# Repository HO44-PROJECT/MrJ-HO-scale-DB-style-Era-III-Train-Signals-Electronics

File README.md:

# Railway HO project Signals and electronics for my HO scale railway project

This is my own project for building model railway HO scale (1:87) Deutsche Bundesbahn (DB) style Era III (1945-1970) Train Signals following this specification.

This is part of a complete project involving:

- 3D printing ([Maker World](https://makerworld.com/en/models/682526#profileId-611046))
- Electronics (PCB design and soldering) ([github](https://github.com/HO44-PROJECT/MrJ-HO-scale-DB-style-Era-III-Train-Signals-Electronics))
- Arduino code (demo, DCC and JMRI integration) ([github](https://github.com/HO44-PROJECT/MrJ-HO-scale-DB-style-Era-III-Train-Signals-Arduino-Demo-Code))

# Resources

[wikipedia signals in Germany](https://en.wikipedia.org/wiki/Railway_signals_in_Germany)

These sites were a great source of inspiration:
* [stummi forum (DE)](https://www.stummiforum.de/t174376f21-Viessman-Signalbr-cke-mit-Arduino-gesteuert.html)
* [digital bahn (DE)] (https://www.digital-bahn.de/info_kompo/signale.htm)

# Project

This project contains Kicad project files and gerber to build PCBs using 1.8mm LEDs.

This PCB uses charlieplexing to reduce the number of wires. It is possible to build a block signal, input signal, or output signal with this PCB.
I designed my own wiring path to avoid using the POV effect to light multiple LEDs. Each situation for each signal is a simple combination of HIGH and LOW signals on all 4 pins.

It's possible to reduce the number of wires for the "Block Signal" (only 2 wires required) and the "Entry Signal" (only 3 wires required). See [documentation/] (documentation/)

I also need a special breadboard version to ease tests. This version allows soldering of resistors.

The **gerber.zip** files are enough to build the PCB from a manufacturer such as [jlcpcb](https://jlcpcb.com/). See [release/] (release/) directory.

# History

The version 2 is smaller than the version 1.
It solves the "shunting signal" Hp0 + Sh1 did not work because the right white LED did not light up.

This v3 is a better version as it fixes a distributed current problem.

# Source

The [source/] directory contains Kicad files

# BOM:
* a PCB per signal. I ordered mine 0.8mm thickness from jlcpcb.com simply by uploading the gerber.zip file.
* 2 to 4 60 to 100 ohm resistors 1/4 W from everywhere
* 1.8mm LEDs. I bought mine from aliexpress.com.

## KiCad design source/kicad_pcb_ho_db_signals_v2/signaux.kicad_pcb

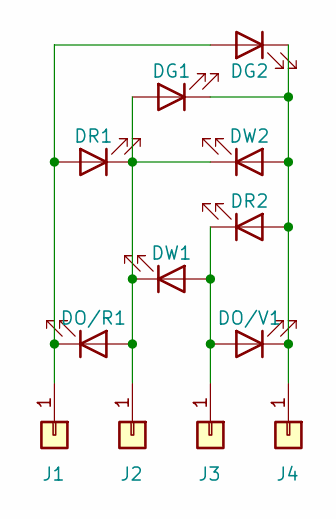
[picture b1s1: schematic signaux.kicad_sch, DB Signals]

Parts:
DG1, DG2: LED; LED_D1.8mm_W3.3mm_H2.4mm_mine
DO/R1: LED; LED_D1.8mm_W3.3mm_H2.4mm_mine
DO/V1: LED; LED_D1.8mm_W3.3mm_H2.4mm_mine
DR1, DR2: LED; LED_D1.8mm_W3.3mm_H2.4mm_mine
DW1, DW2: LED; LED_D1.8mm_W3.3mm_H2.4mm_mine
J1, J2, J3, J4: Conn_01x01; SolderWirePad_1x01_SMD_1x2mm

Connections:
unnamed: DG1.2 (A), DO/R1.2 (A), DR1.1 (K), DW1.1 (K), DW2.1 (K), J2.1
unnamed: DG1.1 (K), DG2.1 (K), DO/V1.1 (K), DR2.2 (A), DW2.2 (A), J4.1
unnamed: DG2.2 (A), DO/R1.1 (K), DR1.2 (A), J1.1
unnamed: DO/V1.2 (A), DR2.1 (K), DW1.2 (A), J3.1

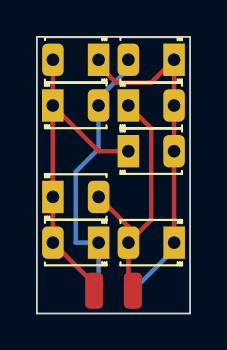
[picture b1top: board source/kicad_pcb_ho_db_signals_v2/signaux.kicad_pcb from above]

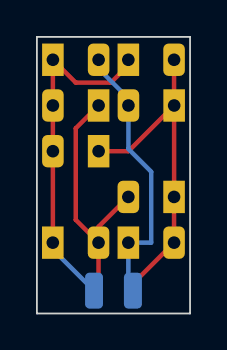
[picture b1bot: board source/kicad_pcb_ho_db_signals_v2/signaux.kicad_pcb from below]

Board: 2 copper layers, 8.5 x 15.4 mm, 12 parts (2 on the bottom side), 4 nets.

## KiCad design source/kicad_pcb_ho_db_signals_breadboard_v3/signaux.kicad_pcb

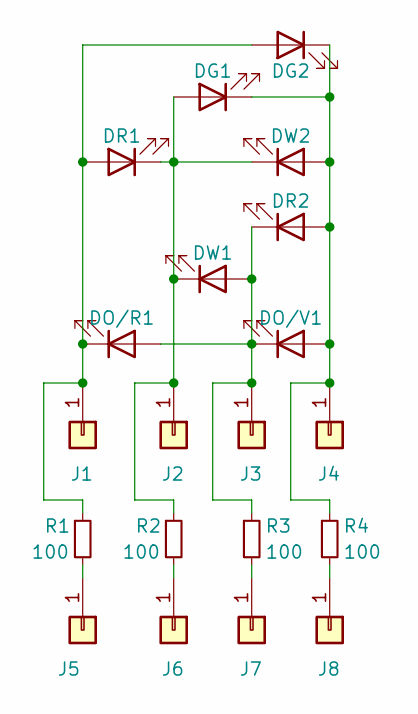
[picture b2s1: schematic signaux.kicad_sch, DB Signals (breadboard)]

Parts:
DG1, DG2: LED; LED_D1.8mm_W3.3mm_H2.4mm_mine
DO/R1: LED; LED_D1.8mm_W3.3mm_H2.4mm_mine
DO/V1: LED; LED_D1.8mm_W3.3mm_H2.4mm_mine
DR1, DR2: LED; LED_D1.8mm_W3.3mm_H2.4mm_mine
DW1, DW2: LED; LED_D1.8mm_W3.3mm_H2.4mm_mine
J1, J2, J3, J4: Conn_01x01; SolderWirePad_1x01_SMD_1x2mm
J5, J6, J7, J8: Conn_01x01; Pin_D0.9mm_L10.0mm_W2.4mm_FlatFork
R1, R2, R3, R4: 100; R_Axial_DIN0204_L3.6mm_D1.6mm_P7.62mm_Horizontal

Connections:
unnamed: DG1.2 (A), DR1.1 (K), DW1.1 (K), DW2.1 (K), J2.1, R2.1
unnamed: DG1.1 (K), DG2.1 (K), DO/V1.2 (A), DR2.2 (A), DW2.2 (A), J4.1, R4.1
unnamed: DG2.2 (A), DO/R1.1 (K), DR1.2 (A), J1.1, R1.1
unnamed: DO/R1.2 (A), DO/V1.1 (K), DR2.1 (K), DW1.2 (A), J3.1, R3.1
unnamed: J5.1, R1.2
unnamed: J6.1, R2.2
unnamed: J7.1, R3.2
unnamed: J8.1, R4.2

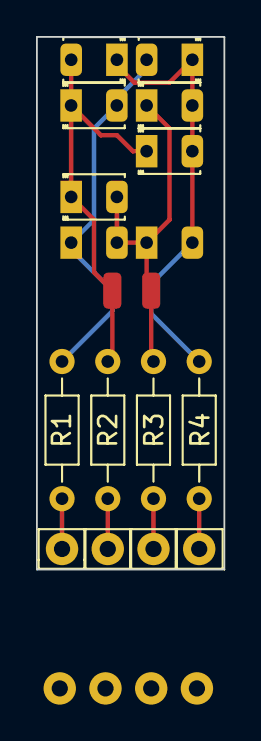
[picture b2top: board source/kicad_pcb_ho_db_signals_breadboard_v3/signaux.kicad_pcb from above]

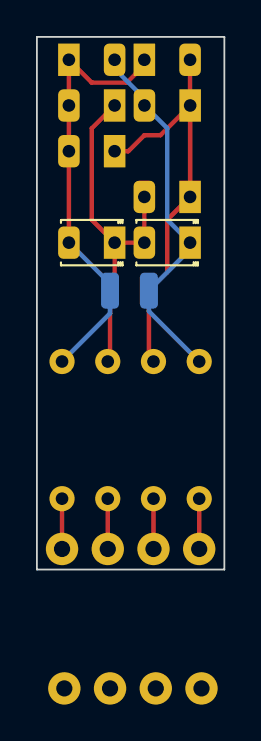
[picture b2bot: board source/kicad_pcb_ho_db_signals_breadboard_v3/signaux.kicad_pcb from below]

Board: 2 copper layers, 10.4 x 29.6 mm, 20 parts (4 on the bottom side), 8 nets.

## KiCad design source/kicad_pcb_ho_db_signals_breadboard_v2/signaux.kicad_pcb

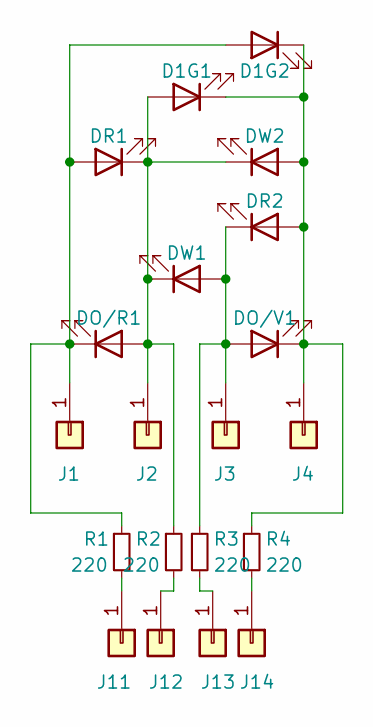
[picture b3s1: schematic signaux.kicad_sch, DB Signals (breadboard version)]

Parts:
D1G1, D1G2: LED; LED_D1.8mm_W3.3mm_H2.4mm_mine
DO/R1: LED; LED_D1.8mm_W3.3mm_H2.4mm_mine
DO/V1: LED; LED_D1.8mm_W3.3mm_H2.4mm_mine
DR1, DR2: LED; LED_D1.8mm_W3.3mm_H2.4mm_mine
DW1, DW2: LED; LED_D1.8mm_W3.3mm_H2.4mm_mine
J1, J2, J3, J4: Conn_01x01; SolderWirePad_1x01_SMD_1x2mm
J11, J12, J13, J14: Conn_01x01; Pin_D0.9mm_L10.0mm_W2.4mm_FlatFork
R1, R2, R3, R4: 220; R_Axial_DIN0204_L3.6mm_D1.6mm_P7.62mm_Horizontal

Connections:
unnamed: D1G1.2 (A), DO/R1.2 (A), DR1.1 (K), DW1.1 (K), DW2.1 (K), J2.1, R2.1
unnamed: D1G1.1 (K), D1G2.1 (K), DO/V1.1 (K), DR2.2 (A), DW2.2 (A), J4.1, R4.1
unnamed: D1G2.2 (A), DO/R1.1 (K), DR1.2 (A), J1.1, R1.1
unnamed: DO/V1.2 (A), DR2.1 (K), DW1.2 (A), J3.1, R3.1
unnamed: J11.1, R1.2
unnamed: J12.1, R2.2
unnamed: J13.1, R3.2
unnamed: J14.1, R4.2

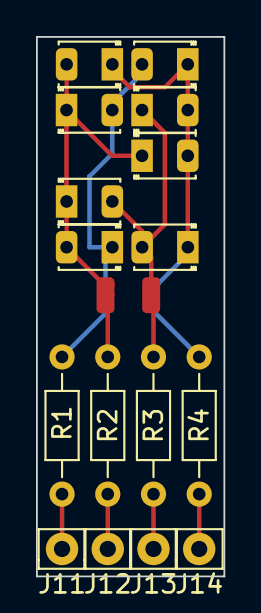
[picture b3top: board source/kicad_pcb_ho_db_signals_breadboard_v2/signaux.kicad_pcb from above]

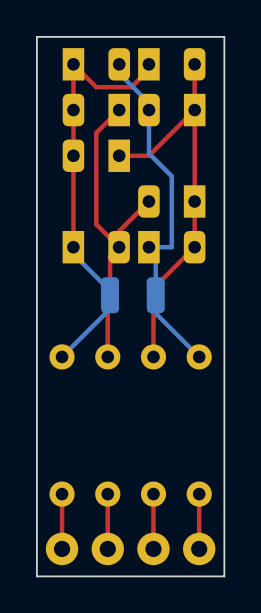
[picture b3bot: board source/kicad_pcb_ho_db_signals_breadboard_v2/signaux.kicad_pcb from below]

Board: 2 copper layers, 10.4 x 30.0 mm, 20 parts (2 on the bottom side), 8 nets.

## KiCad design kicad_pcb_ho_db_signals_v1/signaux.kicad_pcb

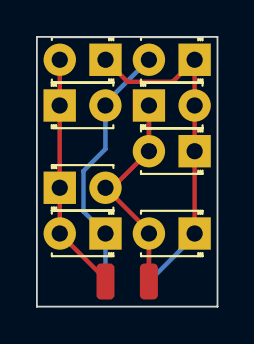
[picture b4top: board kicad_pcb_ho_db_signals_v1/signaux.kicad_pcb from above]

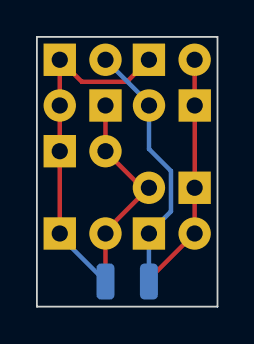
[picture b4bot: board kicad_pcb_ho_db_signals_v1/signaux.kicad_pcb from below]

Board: 2 copper layers, 10.0 x 15.0 mm, 12 parts (2 on the bottom side), 4 nets.

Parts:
D1G1, D1G2, D2R1, D3R1, D4W1, D5W1, D6O1, D7O2: LED; LED_D1.8mm_W3.3mm_H2.4mm
J1, J2, J3, J4: Conn_01x01; SolderWirePad_1x01_SMD_1x2mm

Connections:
unnamed: D1G1.2 (A), D2R1.1 (K), D5W1.1 (K), D6O1.2 (A), J2.1
unnamed: D1G1.1 (K), D1G2.1 (K), D3R1.2 (A), D4W1.1 (K), D7O2.1 (K), J4.1
unnamed: D1G2.2 (A), D2R1.2 (A), D6O1.1 (K), J1.1
unnamed: D3R1.1 (K), D4W1.2 (A), D5W1.2 (A), D7O2.2 (A), J3.1

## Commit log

2024-02-17 first shot
2024-10-03 addon
2024-10-03 gerber files
2024-10-05 reorganisation
2024-10-05 work
2024-10-08 Create LICENSE
2024-10-19 Documentation
2024-10-19 reorg
